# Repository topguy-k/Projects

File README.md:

# Projects
I keep all my projects archived here

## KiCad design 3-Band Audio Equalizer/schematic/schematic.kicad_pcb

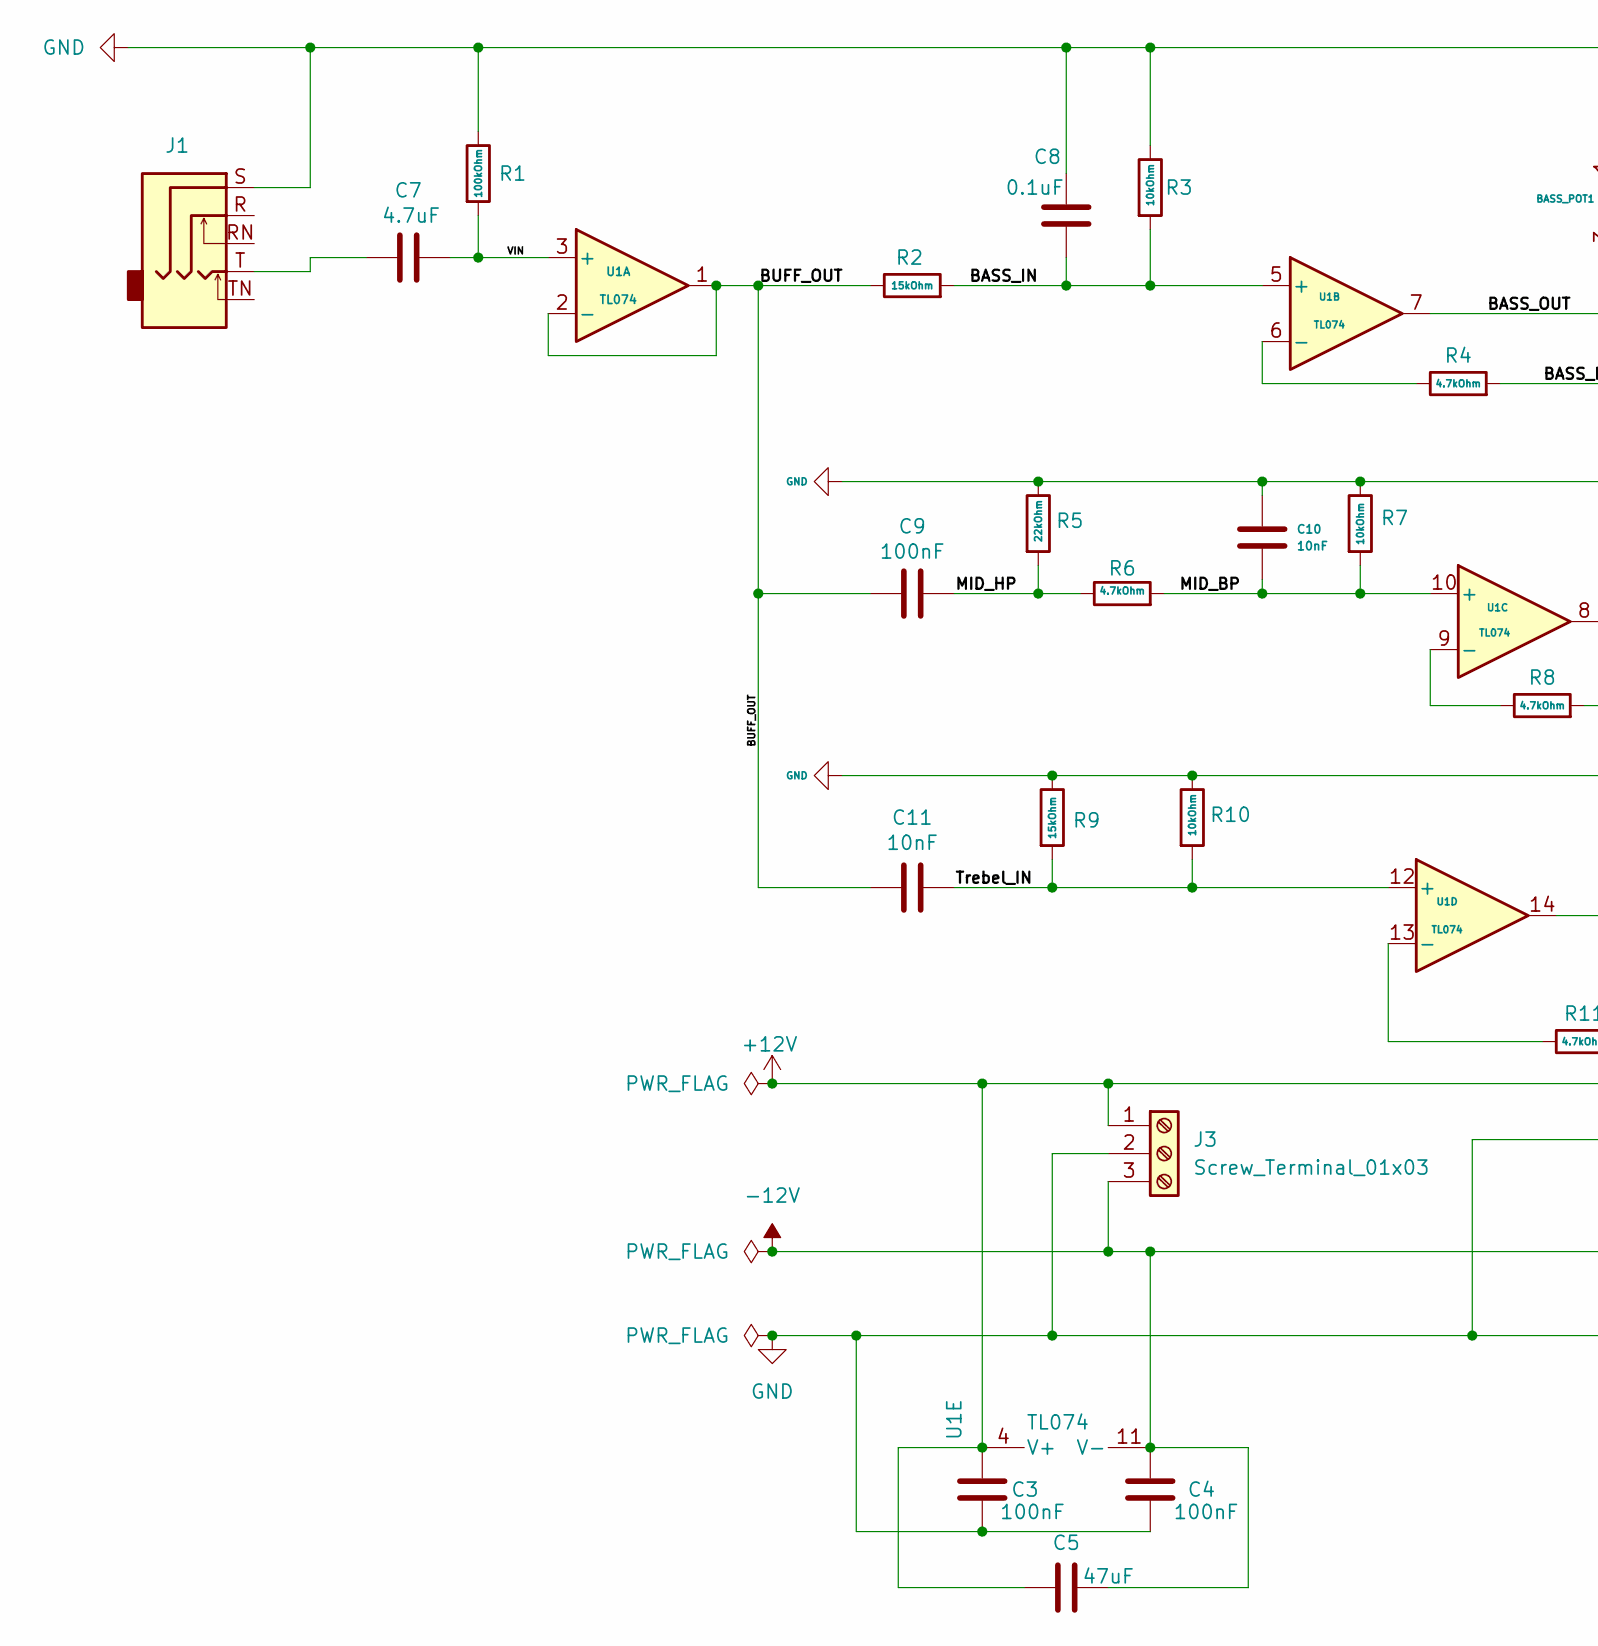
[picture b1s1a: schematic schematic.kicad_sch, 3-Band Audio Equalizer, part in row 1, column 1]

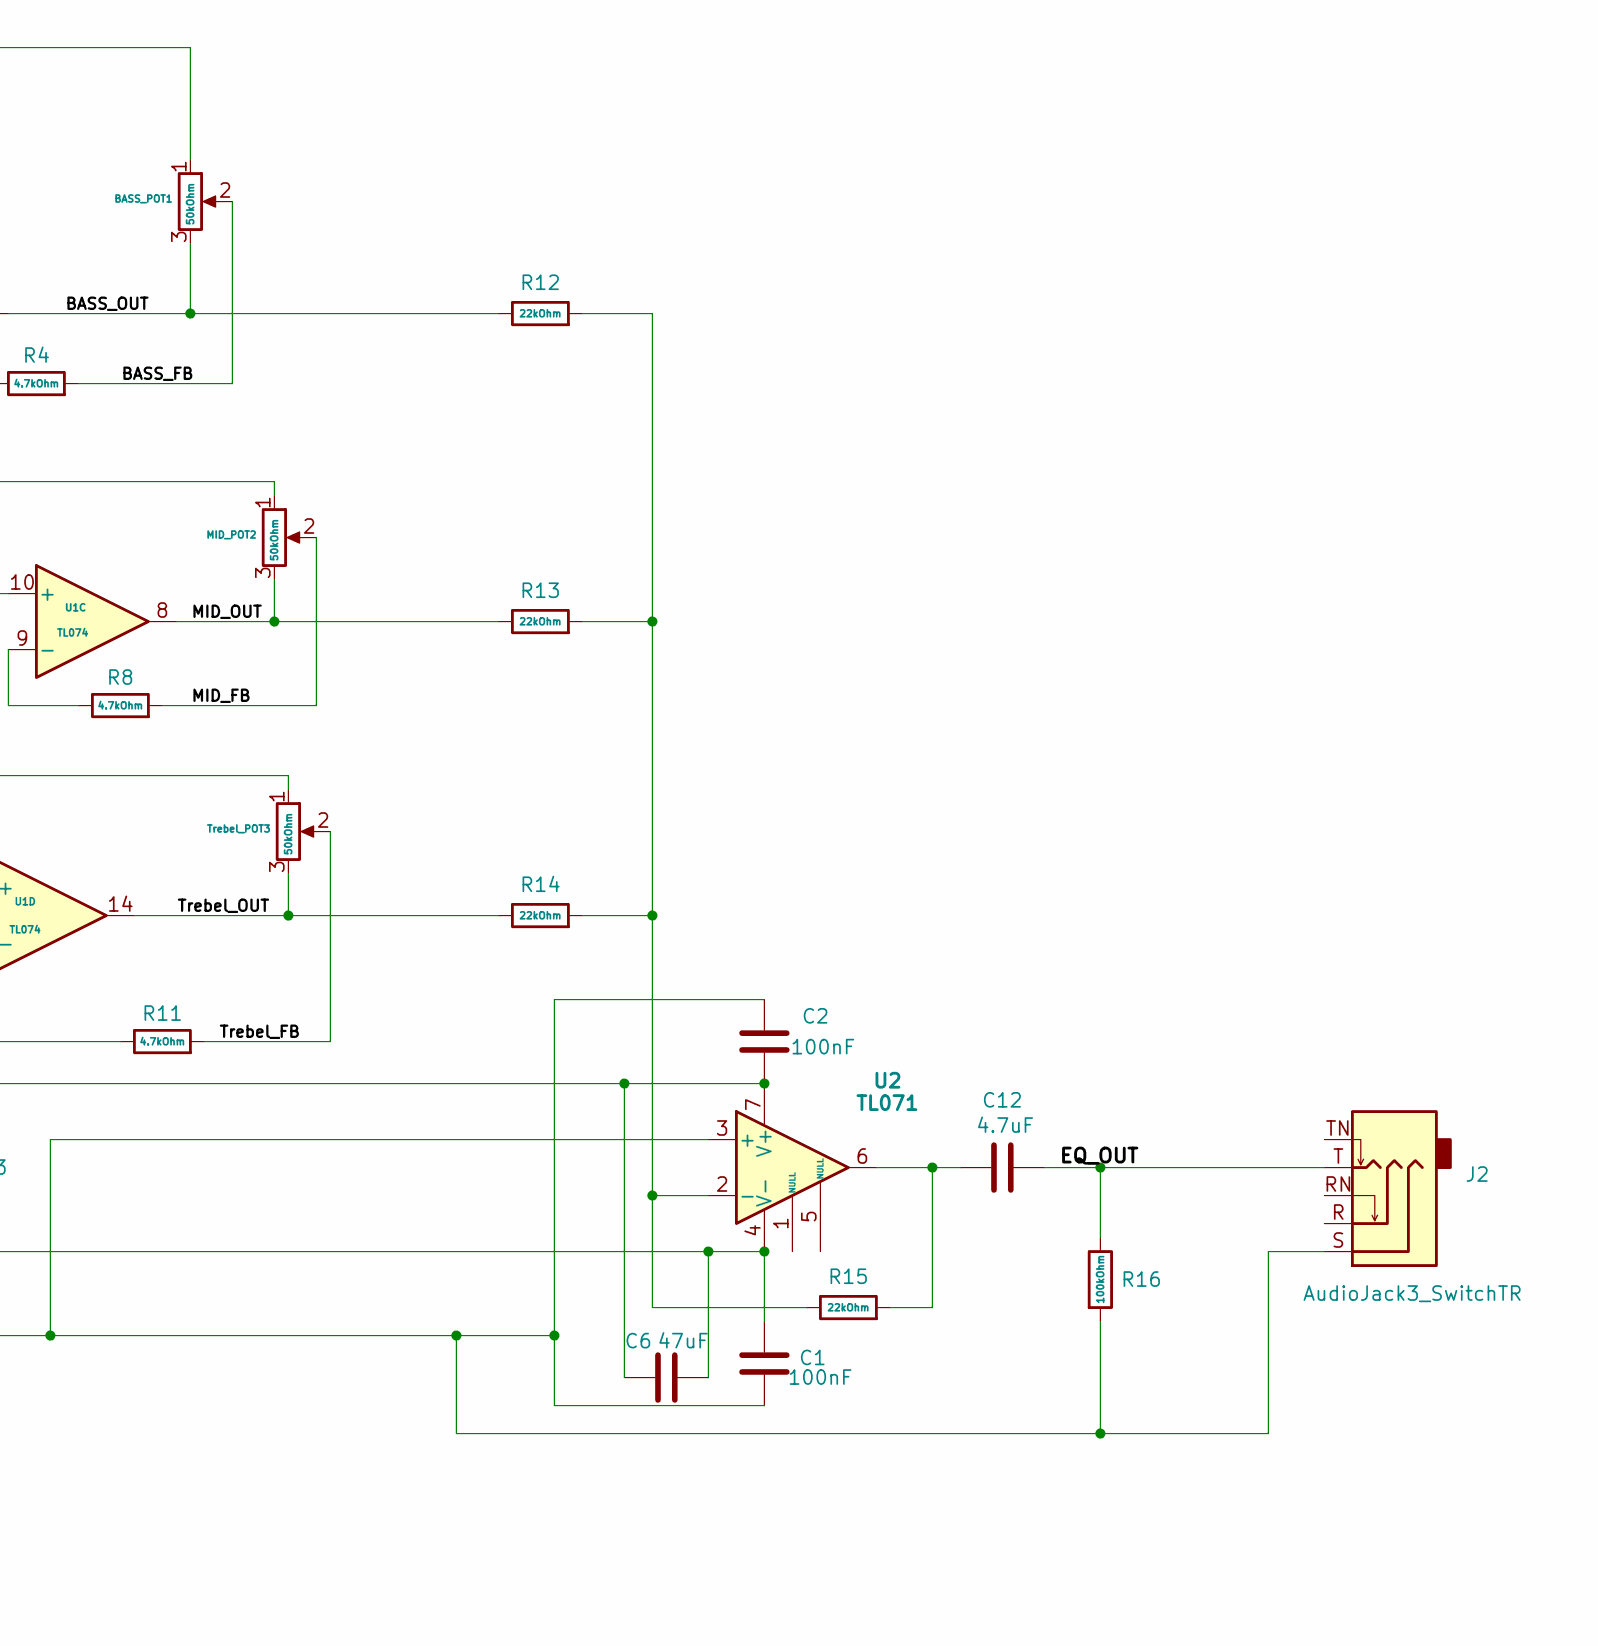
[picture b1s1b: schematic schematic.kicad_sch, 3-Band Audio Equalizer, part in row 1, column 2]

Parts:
BASS_POT1: 50kOhm; Potentiometer_Bourns_3266Z_Horizontal
C1, C2, C3, C4: 100nF; C_Disc_D5.0mm_W2.5mm_P5.00mm
C5, C6: 47uF; CP_Radial_D8.0mm_P5.00mm
C7, C12: 4.7uF; CP_Radial_D6.3mm_P2.50mm
C8: 0.1uF; C_Radial_D6.3mm_H5.0mm_P2.50mm
C9: 100nF; C_Radial_D6.3mm_H5.0mm_P2.50mm
C10, C11: 10nF; C_Radial_D6.3mm_H5.0mm_P2.50mm
J1, J2: AudioJack3_SwitchTR; Jack_3.5mm_CUI_SJ1-3525N_Horizontal
J3: Screw_Terminal_01x03; TerminalBlock_Phoenix_MPT-0,5-3-2.54_1x03_P2.54mm_Horizontal
MID_POT2: 50kOhm; Potentiometer_Bourns_3266Z_Horizontal
R1, R16: 100kOhm; R_Axial_DIN0207_L6.3mm_D2.5mm_P7.62mm_Horizontal
R2, R9: 15kOhm; R_Axial_DIN0207_L6.3mm_D2.5mm_P7.62mm_Horizontal
R3, R7, R10: 10kOhm; R_Axial_DIN0207_L6.3mm_D2.5mm_P7.62mm_Horizontal
R4, R6, R8, R11: 4.7kOhm; R_Axial_DIN0207_L6.3mm_D2.5mm_P7.62mm_Horizontal
R5, R12, R13, R14, R15: 22kOhm; R_Axial_DIN0207_L6.3mm_D2.5mm_P7.62mm_Horizontal
Trebel_POT3: 50kOhm; Potentiometer_Bourns_3266Z_Horizontal
U1: TL074; DIP-14_W7.62mm
U2: TL071; DIP-8_W7.62mm

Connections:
+12V: C2.2, C3.1, C5.1, C6.2, J3.1, U1.4 (V+), U2.7 (V+)
-12V: C1.1, C4.1, C5.2, C6.1, J3.3, U1.11 (V-), U2.4 (V-)
/BASS_FB: BASS_POT1.2, R4.2
/BASS_IN: C8.2, R2.2, R3.2, U1.5 (+)
/BASS_OUT: BASS_POT1.3, R12.1, U1.7
/BUFF_OUT: C9.2, C11.1, R2.1, U1.1, U1.2 (-)
/EQ_OUT: C12.2, J2.T, R16.1
/MID_BP: C10.2, R6.2, R7.2, U1.10 (+)
/MID_FB: MID_POT2.2, R8.2
/MID_HP: C9.1, R5.2, R6.1
/MID_OUT: MID_POT2.3, R13.1, U1.8
/Trebel_FB: R11.2, Trebel_POT3.2
/Trebel_IN: C11.2, R9.2, R10.2, U1.12 (+)
/Trebel_OUT: R14.1, Trebel_POT3.3, U1.14
/VIN: C7.2, R1.2, U1.3 (+)
GND: BASS_POT1.1, C1.2, C2.1, C3.2, C4.2, C8.1, C10.1, J1.S, J2.S, J3.2, MID_POT2.1, R1.1, R3.1, R5.1, R7.1, R9.1, R10.1, R16.2, Trebel_POT3.1, U2.3 (+)
unnamed: C7.1, J1.T
unnamed: C12.1, R15.2, U2.6
unnamed: R4.1, U1.6 (-)
unnamed: R8.1, U1.9 (-)
unnamed: R11.1, U1.13 (-)
unnamed: R12.2, R13.2, R14.2, R15.1, U2.2 (-)

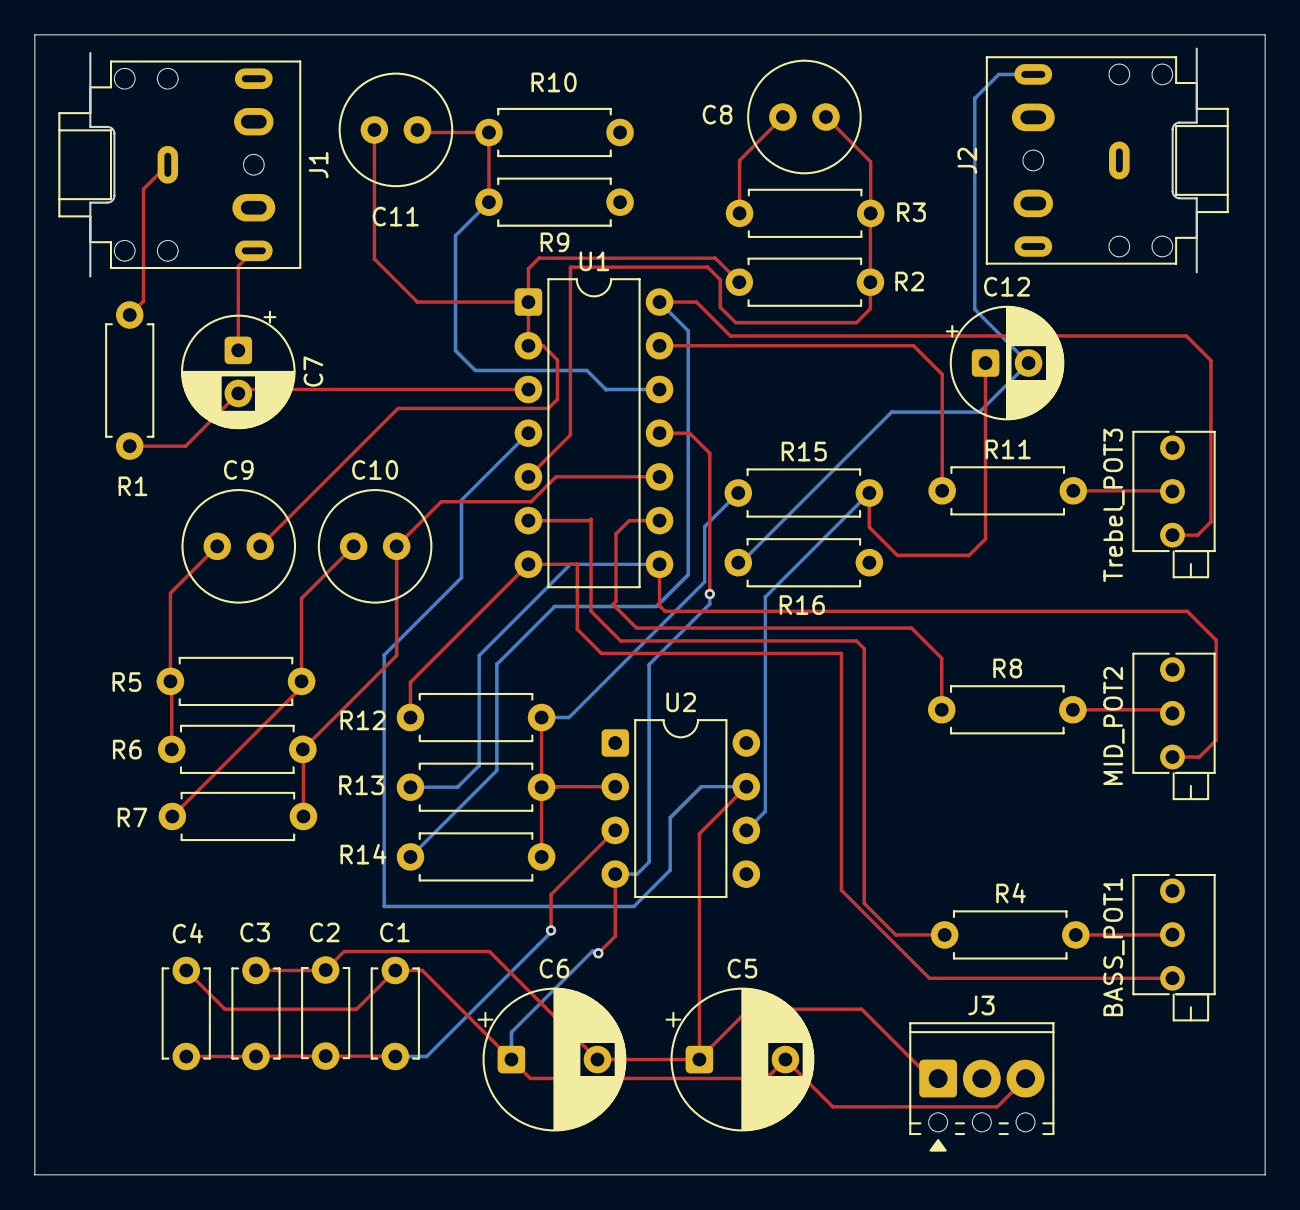
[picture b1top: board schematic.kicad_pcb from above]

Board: 2 copper layers, 71.4 x 66.2 mm, 36 parts (0 on the bottom side), 22 nets.
